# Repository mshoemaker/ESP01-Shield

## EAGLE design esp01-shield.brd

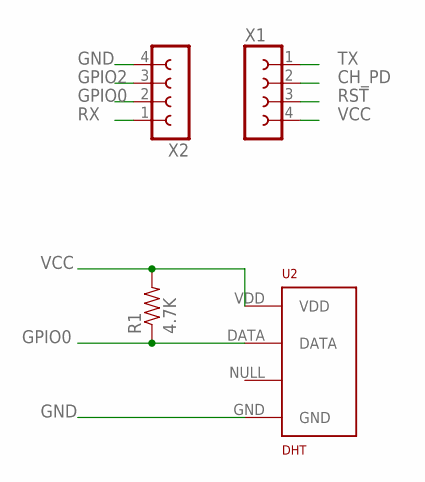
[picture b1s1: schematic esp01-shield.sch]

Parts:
R1: 4.7K; 1/6W-RES
U2: DHT; RHT03_DHT-22
X1, X2: SPB4

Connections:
CH_PD: X1.2
GND: U2.GND, X2.4
GPIO0: R1.1, U2.DATA, X2.2
GPIO2: X2.3
RST: X1.3
RX: X2.1
TX: X1.1
VCC: R1.2, U2.VDD, X1.4

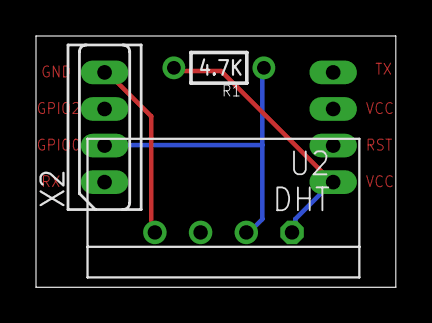
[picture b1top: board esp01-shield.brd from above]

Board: 2 copper layers, 20.0 x 14.0 mm, 4 parts (1 on the bottom side), 3 nets.

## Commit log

2016-10-20 :boom::camel: Added .gitattributes & .gitignore files
2016-10-20 Shield for ESP01-Prog board

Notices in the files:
parts and their libraries:
SparkFun-Passives: Licensing: Creative Commons ShareAlike 4.0 International - https://creativecommons.org/licenses/by-sa/4.0
